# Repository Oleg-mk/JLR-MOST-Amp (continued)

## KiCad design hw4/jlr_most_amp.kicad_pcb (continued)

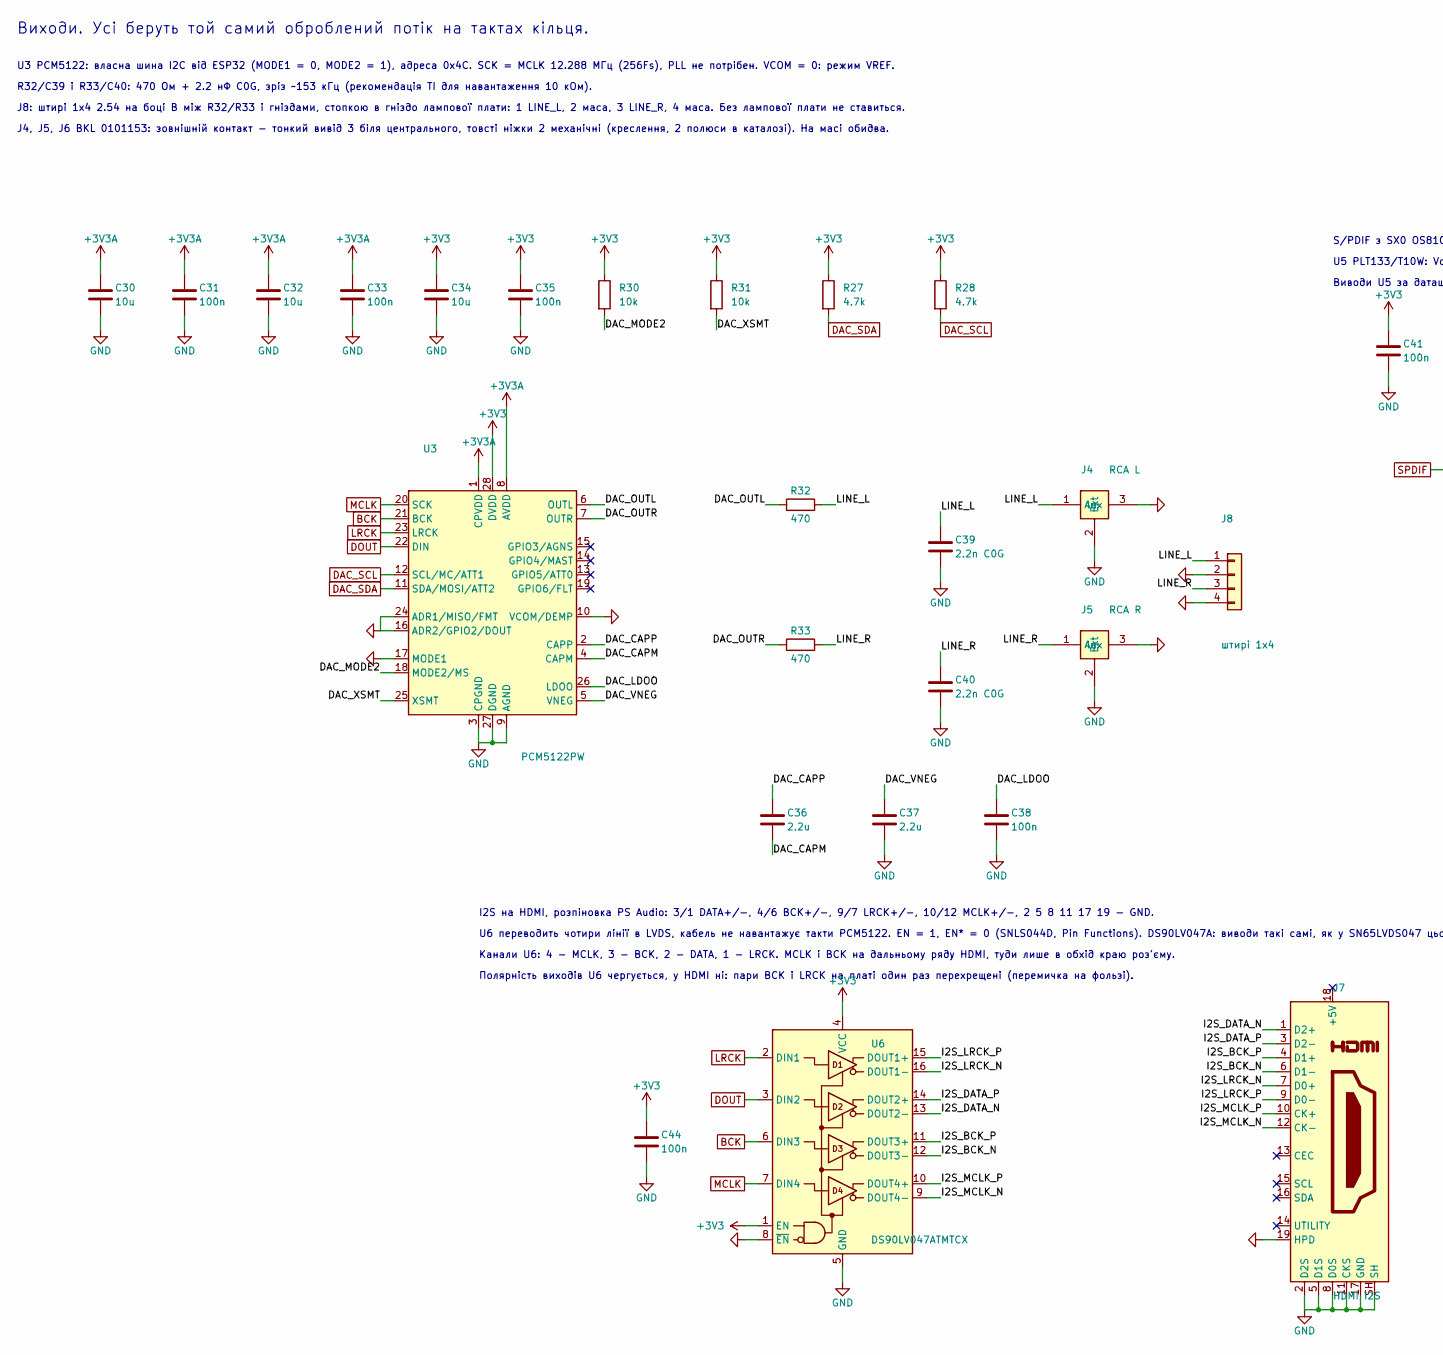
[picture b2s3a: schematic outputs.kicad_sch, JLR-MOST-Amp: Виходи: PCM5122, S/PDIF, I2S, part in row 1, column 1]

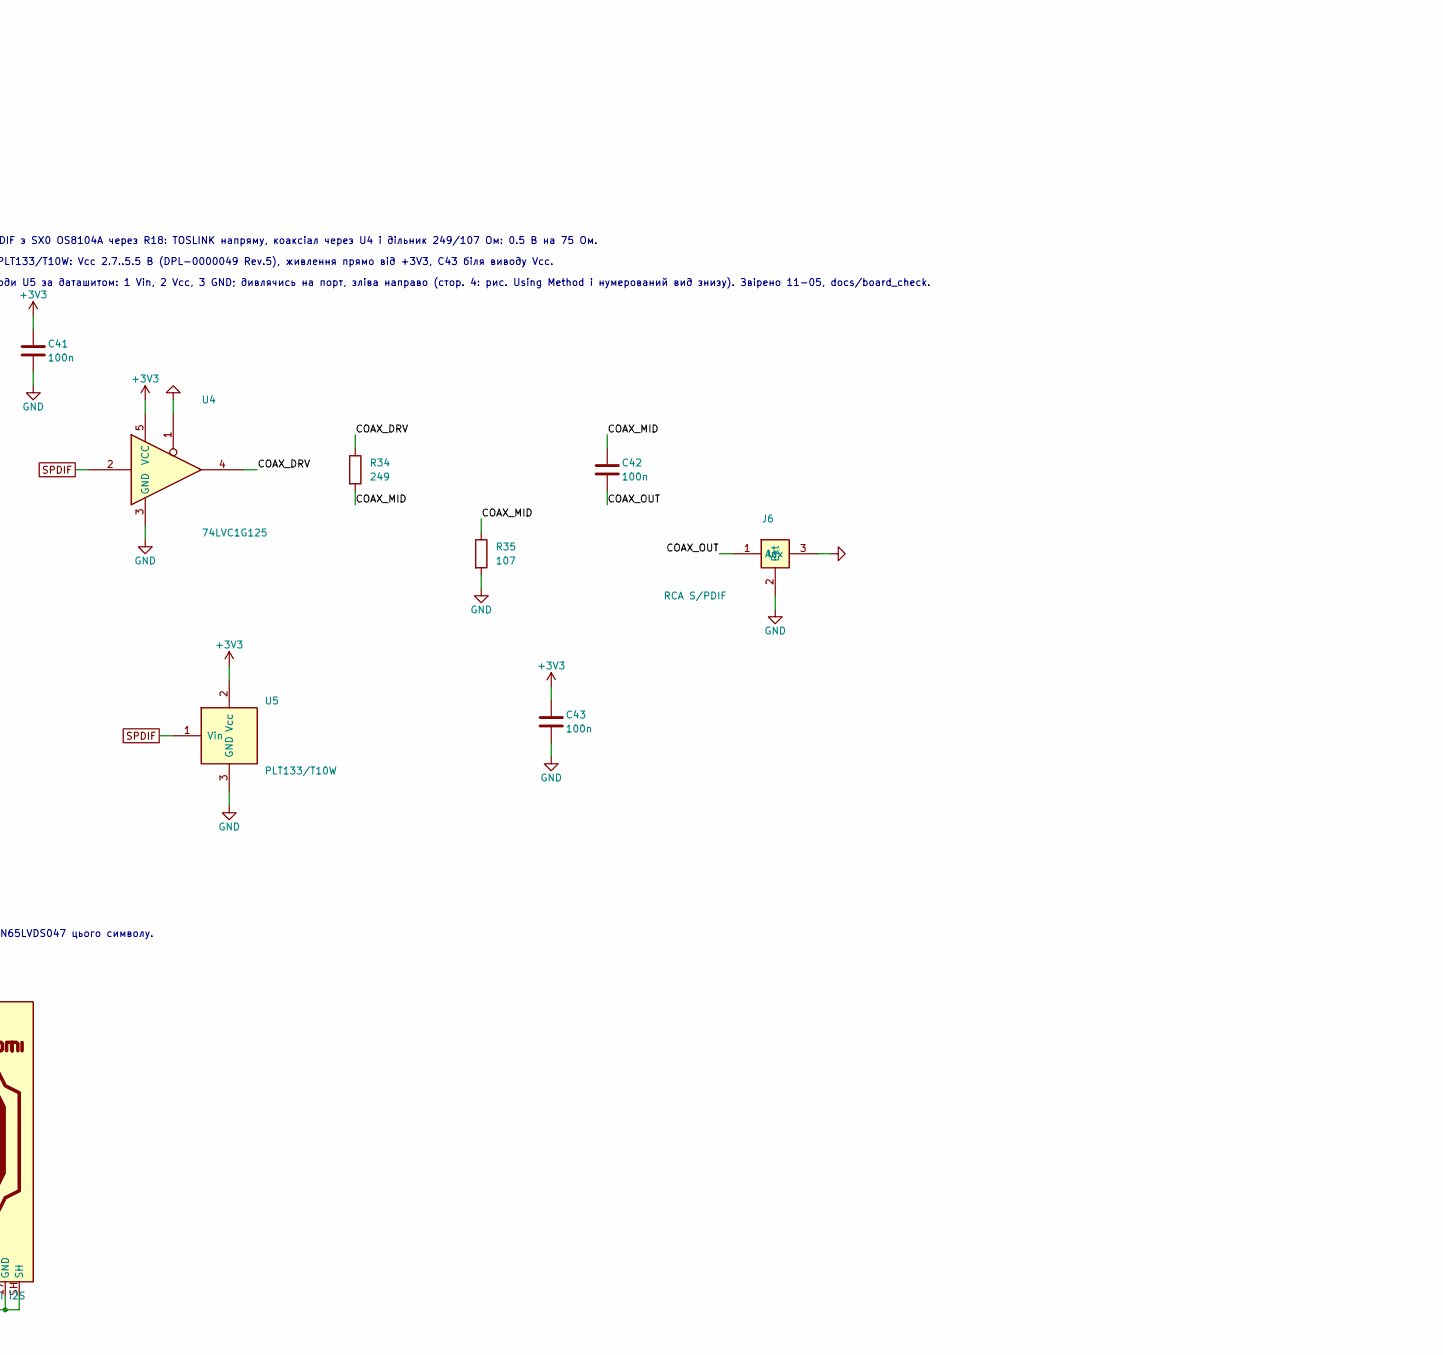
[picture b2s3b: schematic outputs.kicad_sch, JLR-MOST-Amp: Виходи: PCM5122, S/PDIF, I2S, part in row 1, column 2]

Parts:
C30, C32, C34: 10u; C_0805_2012Metric
C31, C33, C35, C38, C41, C42, C43, C44: 100n; C_0603_1608Metric
C36, C37: 2.2u; C_0805_2012Metric
C39, C40: 2.2n C0G; C_0603_1608Metric
J4: RCA L; BKL_0101153_RCA_RA
J5: RCA R; BKL_0101153_RCA_RA
J6: RCA S/PDIF; BKL_0101153_RCA_RA
J7: HDMI I2S; HDMI_A_Kycon_KDMIX-SL1-NS-WS-B15_VerticalRightAngle
J8: штирі 1x4; PinHeader_1x04_P2.54mm_Vertical
R27, R28: 4.7k; R_0603_1608Metric
R30, R31: 10k; R_0603_1608Metric
R32, R33: 470; R_0603_1608Metric
R34: 249; R_0603_1608Metric
R35: 107; R_0603_1608Metric
U3: PCM5122PW; TSSOP-28_4.4x9.7mm_P0.65mm
U4: 74LVC1G125; SOT-23-5
U5: PLT133/T10W; Everlight_TOSLINK_T10
U6: DS90LV047ATMTCX; TSSOP-16_4.4x5mm_P0.65mm

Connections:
+3V3: C34.1, C35.1, C41.1, C43.1, C44.1, R27.1, R28.1, R30.1, R31.1, U3.28 (DVDD), U4.5 (VCC), U5.2 (Vcc), U6.1 (EN), U6.4 (VCC); also elsewhere on the board
+3V3A: C30.1, C31.1, C32.1, C33.1, U3.1 (CPVDD), U3.8 (AVDD); also elsewhere on the board
/Виходи: PCM5122, S/PDIF, I2S/COAX_DRV: R34.1, U4.4
/Виходи: PCM5122, S/PDIF, I2S/COAX_MID: C42.1, R34.2, R35.1
/Виходи: PCM5122, S/PDIF, I2S/COAX_OUT: C42.2, J6.1 (In)
/Виходи: PCM5122, S/PDIF, I2S/DAC_CAPM: C36.2, U3.4 (CAPM)
/Виходи: PCM5122, S/PDIF, I2S/DAC_CAPP: C36.1, U3.2 (CAPP)
/Виходи: PCM5122, S/PDIF, I2S/DAC_LDOO: C38.1, U3.26 (LDOO)
/Виходи: PCM5122, S/PDIF, I2S/DAC_MODE2: R30.2, U3.18 (MODE2/MS)
/Виходи: PCM5122, S/PDIF, I2S/DAC_OUTL: R32.1, U3.6 (OUTL)
/Виходи: PCM5122, S/PDIF, I2S/DAC_OUTR: R33.1, U3.7 (OUTR)
/Виходи: PCM5122, S/PDIF, I2S/DAC_VNEG: C37.1, U3.5 (VNEG)
/Виходи: PCM5122, S/PDIF, I2S/DAC_XSMT: R31.2, U3.25 (XSMT)
/Виходи: PCM5122, S/PDIF, I2S/I2S_BCK_N: J7.6 (D1-), U6.12 (DOUT3-)
/Виходи: PCM5122, S/PDIF, I2S/I2S_BCK_P: J7.4 (D1+), U6.11 (DOUT3+)
/Виходи: PCM5122, S/PDIF, I2S/I2S_DATA_N: J7.1 (D2+), U6.13 (DOUT2-)
/Виходи: PCM5122, S/PDIF, I2S/I2S_DATA_P: J7.3 (D2-), U6.14 (DOUT2+)
/Виходи: PCM5122, S/PDIF, I2S/I2S_LRCK_N: J7.7 (D0+), U6.16 (DOUT1-)
/Виходи: PCM5122, S/PDIF, I2S/I2S_LRCK_P: J7.9 (D0-), U6.15 (DOUT1+)
/Виходи: PCM5122, S/PDIF, I2S/I2S_MCLK_N: J7.12 (CK-), U6.9 (DOUT4-)
/Виходи: PCM5122, S/PDIF, I2S/I2S_MCLK_P: J7.10 (CK+), U6.10 (DOUT4+)
/Виходи: PCM5122, S/PDIF, I2S/LINE_L: C39.1, J4.1 (In), J8.1, R32.2
/Виходи: PCM5122, S/PDIF, I2S/LINE_R: C40.1, J5.1 (In), J8.3, R33.2
BCK: U3.21 (BCK), U6.6 (DIN3); also elsewhere on the board
DAC_SCL: R28.2, U3.12 (SCL/MC/ATT1); also elsewhere on the board
DAC_SDA: R27.2, U3.11 (SDA/MOSI/ATT2); also elsewhere on the board
DOUT: U3.22 (DIN), U6.3 (DIN2); also elsewhere on the board
GND: C30.2, C31.2, C32.2, C33.2, C34.2, C35.2, C37.2, C38.2, C39.2, C40.2, C41.2, C43.2, C44.2, J4.2 (Ext), J4.3 (Aux), J5.2 (Ext), J5.3 (Aux), J6.2 (Ext), J6.3 (Aux), J7.2 (D2S), J7.5 (D1S), J7.8 (D0S), J7.11 (CKS), J7.17 (GND), J7.19 (HPD), J7.SH, J8.2, J8.4, R35.2, U3.3 (CPGND), U3.9 (AGND), U3.10 (VCOM/DEMP), U3.16 (ADR2/GPIO2/DOUT), U3.17 (MODE1), U3.24 (ADR1/MISO/FMT), U3.27 (DGND), U4.1, U4.3 (GND), U5.3 (GND), U6.5 (GND), U6.8 (~EN); also elsewhere on the board
LRCK: U3.23 (LRCK), U6.2 (DIN1); also elsewhere on the board
MCLK: U3.20 (SCK), U6.7 (DIN4); also elsewhere on the board
SPDIF: U4.2, U5.1 (Vin); also elsewhere on the board

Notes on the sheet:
Виходи. Усі беруть той самий оброблений потік на тактах кільця.
U3 PCM5122: власна шина I2C від ESP32 (MODE1 = 0, MODE2 = 1), адреса 0x4C. SCK = MCLK 12.288 МГц (256Fs), PLL не потрібен. VCOM = 0: режим VREF.
R32/C39 і R33/C40: 470 Ом + 2.2 нФ C0G, зріз ~153 кГц (рекомендація TI для навантаження 10 кОм).
J8: штирі 1x4 2.54 на боці B між R32/R33 і гніздами, стопкою в гніздо лампової плати: 1 LINE_L, 2 маса, 3 LINE_R, 4 маса. Без лампової плати не ставиться.
S/PDIF з SX0 OS8104A через R18: TOSLINK напряму, коаксіал через U4 і дільник 249/107 Ом: 0.5 В на 75 Ом.
U5 PLT133/T10W: Vcc 2.7..5.5 В (DPL-0000049 Rev.5), живлення прямо від +3V3, C43 біля виводу Vcc.
Виводи U5 за даташитом: 1 Vin, 2 Vcc, 3 GND; дивлячись на порт, зліва направо (стор. 4: рис. Using Method і нумерований вид знизу). Звірено 11-05, docs/board_check.
J4, J5, J6 BKL 0101153: зовнішній контакт - тонкий вивід 3 біля центрального, товсті ніжки 2 механічні (креслення, 2 полюси в каталозі). На масі обидва.
I2S на HDMI, розпіновка PS Audio: 3/1 DATA+/-, 4/6 BCK+/-, 9/7 LRCK+/-, 10/12 MCLK+/-, 2 5 8 11 17 19 - GND.
U6 переводить чотири лінії в LVDS, кабель не навантажує такти PCM5122. EN = 1, EN* = 0 (SNLS044D, Pin Functions). DS90LV047A: виводи такі самі, як у SN65LVDS047 цього символу.
Канали U6: 4 - MCLK, 3 - BCK, 2 - DATA, 1 - LRCK. MCLK і BCK на дальньому ряду HDMI, туди лише в обхід краю роз'єму.
Полярність виходів U6 чергується, у HDMI ні: пари BCK і LRCK на платі один раз перехрещені (перемичка на фользі).

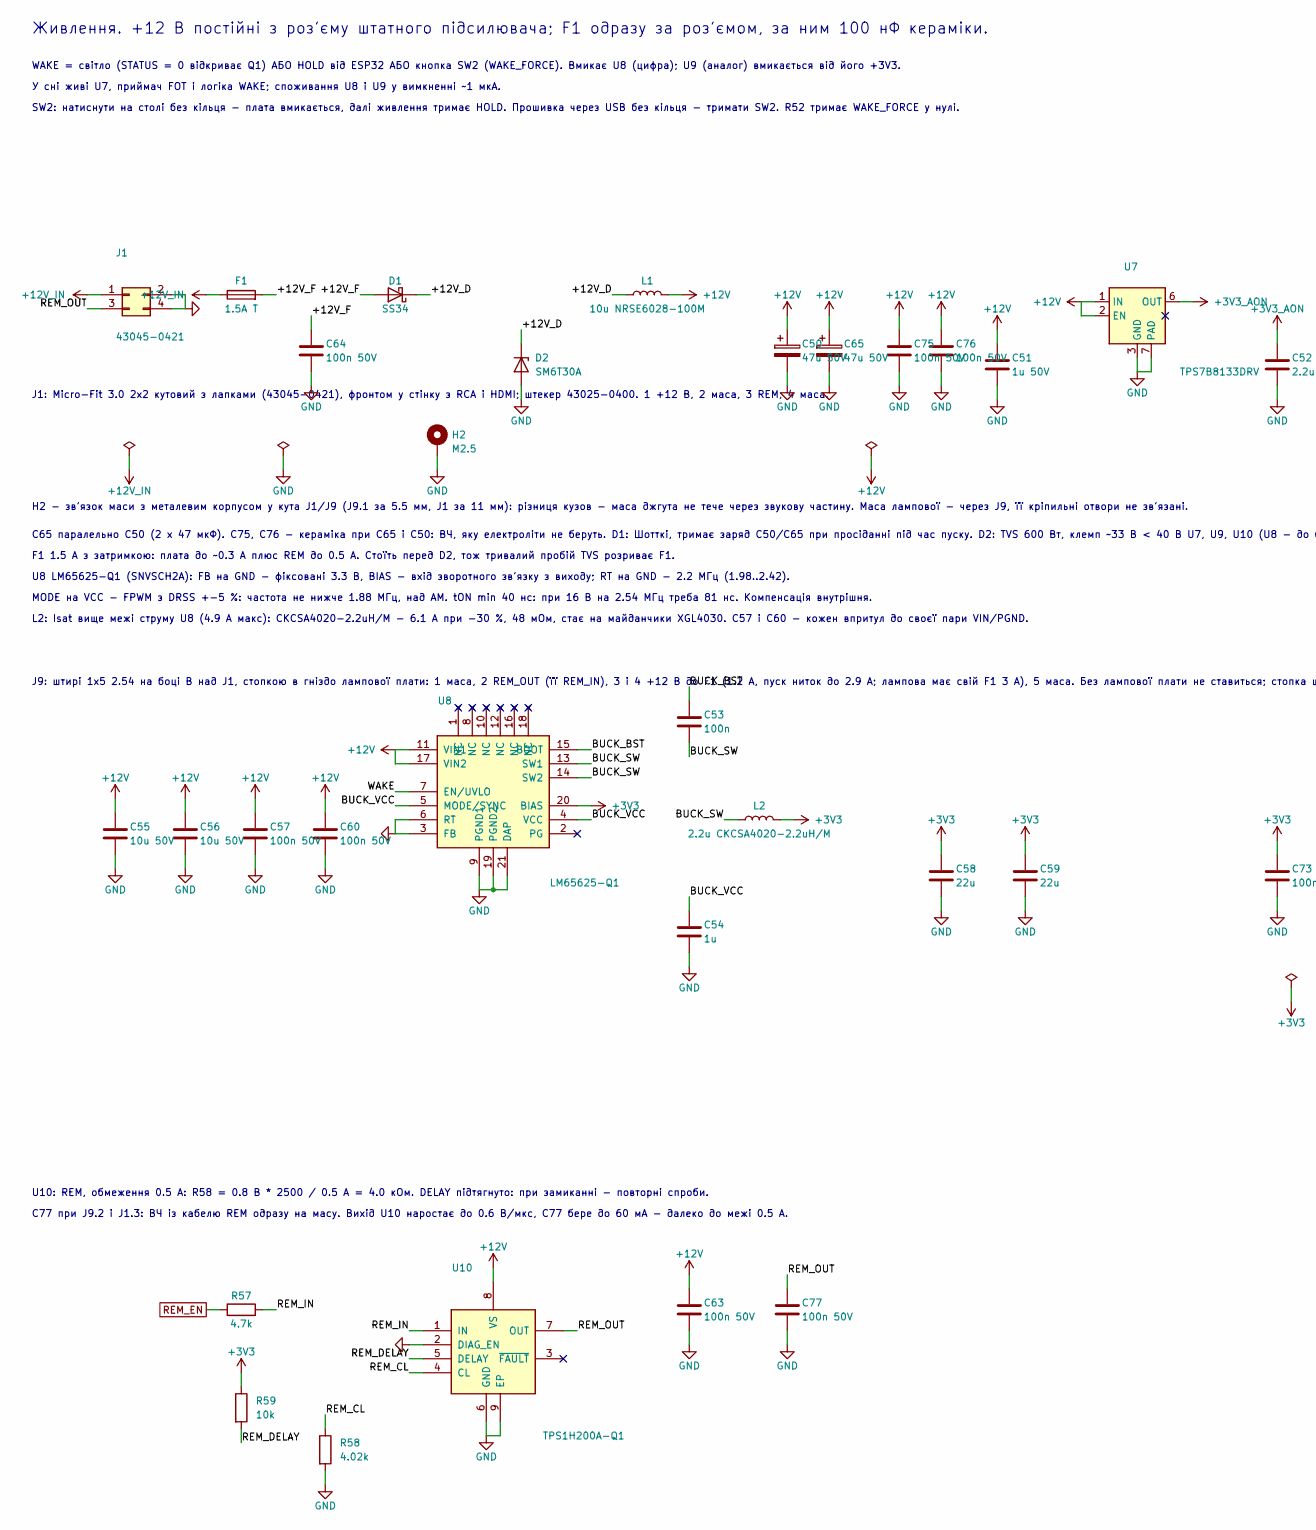
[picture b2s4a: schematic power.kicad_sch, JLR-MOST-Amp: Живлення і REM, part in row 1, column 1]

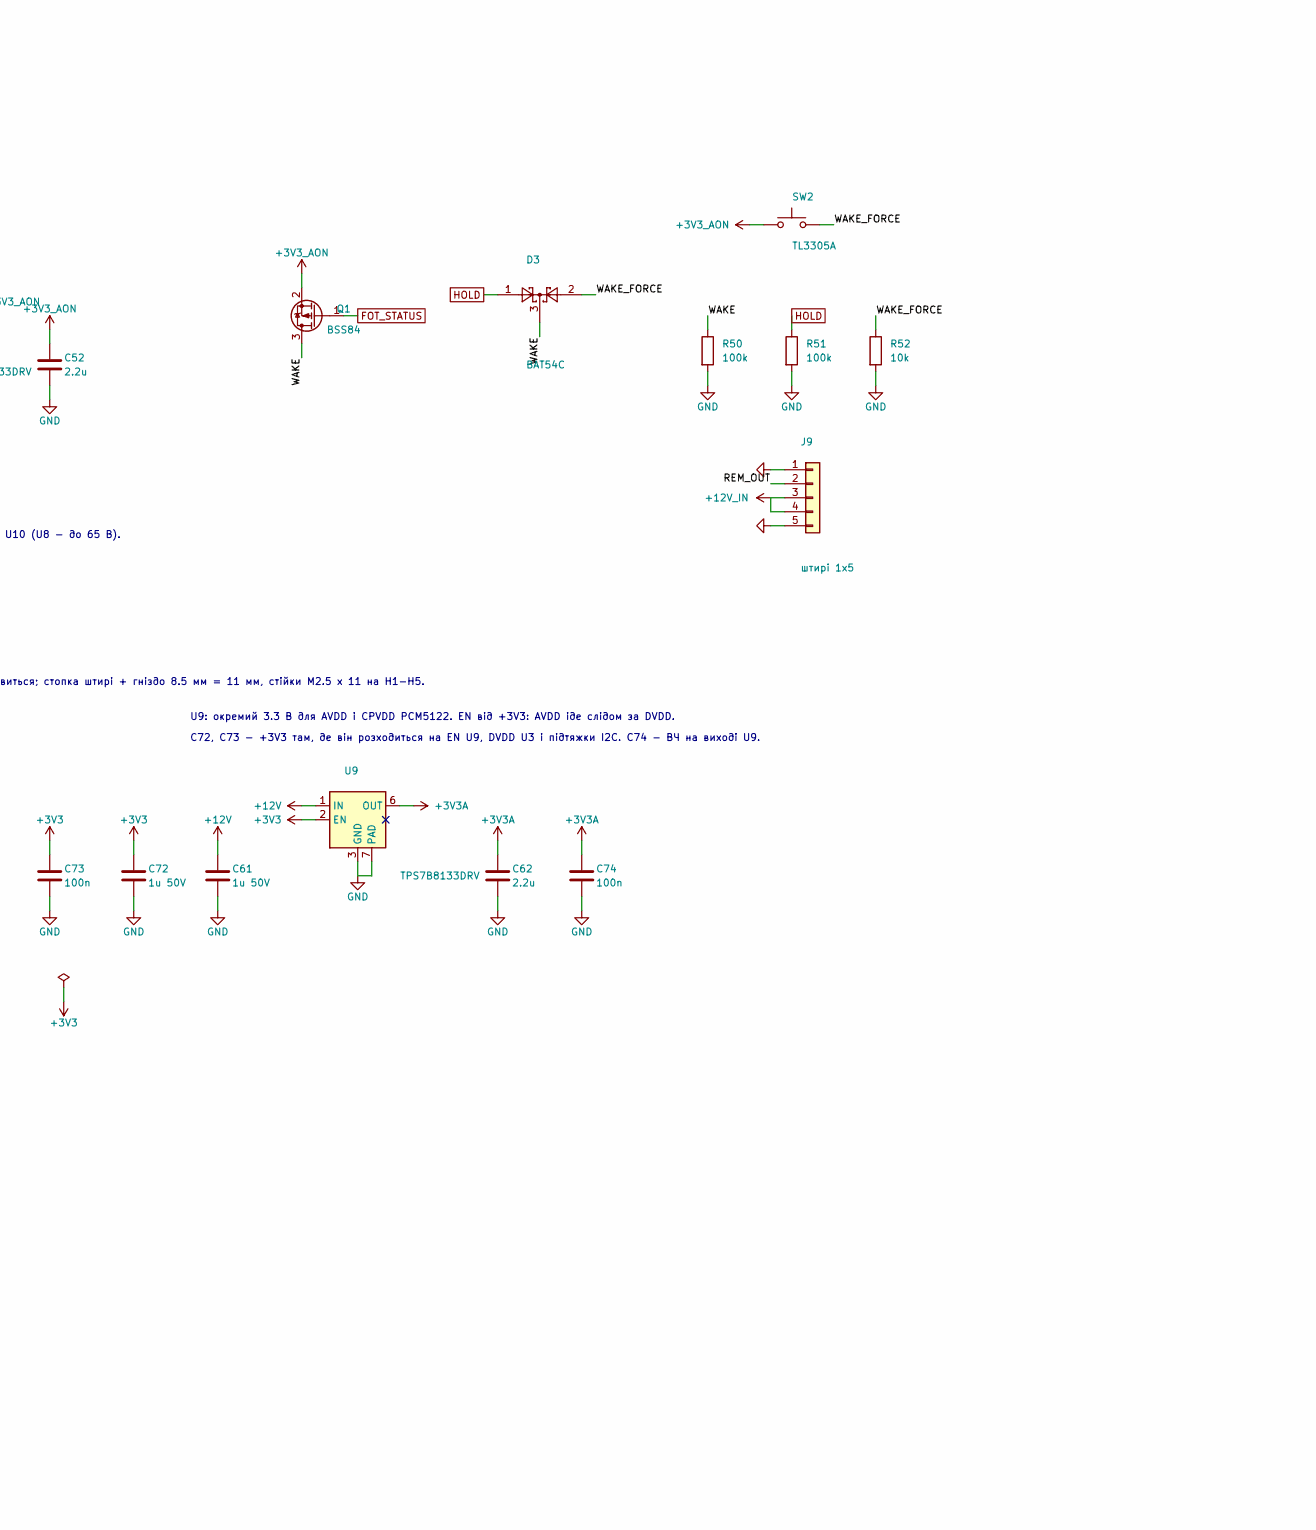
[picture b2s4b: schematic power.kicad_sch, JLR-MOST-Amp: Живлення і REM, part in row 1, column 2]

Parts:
C50, C65: 47u 50V; CP_Elec_8x10
C51, C61, C72: 1u 50V; C_0805_2012Metric
C52, C62: 2.2u; C_0805_2012Metric
C53, C73, C74: 100n; C_0603_1608Metric
C54: 1u; C_0603_1608Metric
C55, C56: 10u 50V; C_1210_3225Metric
C57, C60, C63, C64, C75, C76, C77: 100n 50V; C_0603_1608Metric
C58, C59: 22u; C_1206_3216Metric
D1: SS34; D_SMA
D2: SM6T30A; D_SMB
D3: BAT54C; SOT-23
F1: 1.5A T; Fuse_1206_3216Metric
H2: M2.5; MountingHole_2.7mm_M2.5_Standoff_GND
J1: 43045-0421; Molex_Micro-Fit_3.0_43045-0421_2x02-1MP_P3.00mm_Horizontal
J9: штирі 1x5; PinHeader_1x05_P2.54mm_Vertical
L1: 10u NRSE6028-100M; L_Bourns-SRN6028
L2: 2.2u CKCSA4020-2.2uH/M; L_Coilcraft_XxL4030
Q1: BSS84; SOT-23
R50, R51: 100k; R_0603_1608Metric
R52, R59: 10k; R_0603_1608Metric
R57: 4.7k; R_0603_1608Metric
R58: 4.02k; R_0603_1608Metric
SW2: TL3305A; SW_SPST_TL3305A
U7, U9: TPS7B8133DRV; WSON-6-1EP_2x2mm_P0.65mm_EP1x1.6mm
U8: LM65625-Q1; TI_RZT0020A
U10: TPS1H200A-Q1; HVSSOP-8-1EP_3x3mm_P0.65mm_EP1.57x1.89mm

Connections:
+3V3: C58.1, C59.1, C72.1, C73.1, L2.2, R59.1, U8.20 (BIAS), U9.2 (EN); also elsewhere on the board
+3V3A: C62.1, C74.1, U9.6 (OUT); also elsewhere on the board
+3V3_AON: C52.1, Q1.2 (S), SW2.1, U7.6 (OUT); also elsewhere on the board
+12V: C50.1, C51.1, C55.1, C56.1, C57.1, C60.1, C61.1, C63.1, C65.1, C75.1, C76.1, L1.2, U7.1 (IN), U7.2 (EN), U8.11 (VIN1), U8.17 (VIN2), U9.1 (IN), U10.8 (VS)
+12V_IN: F1.1, J1.1, J9.3, J9.4
/Живлення і REM/+12V_D: D1.1 (K), D2.1 (K), L1.1
/Живлення і REM/+12V_F: C64.1, D1.2 (A), F1.2
/Живлення і REM/BUCK_BST: C53.1, U8.15 (BOOT)
/Живлення і REM/BUCK_SW: C53.2, L2.1, U8.13 (SW1), U8.14 (SW2)
/Живлення і REM/BUCK_VCC: C54.1, U8.4 (VCC), U8.5 (MODE/SYNC)
/Живлення і REM/REM_CL: R58.1, U10.4 (CL)
/Живлення і REM/REM_DELAY: R59.2, U10.5 (DELAY)
/Живлення і REM/REM_IN: R57.2, U10.1 (IN)
/Живлення і REM/REM_OUT: C77.1, J1.3, J9.2, U10.7 (OUT)
/Живлення і REM/WAKE: D3.3, Q1.3 (D), R50.1, U8.7 (EN/UVLO)
/Живлення і REM/WAKE_FORCE: D3.2, R52.1, SW2.2
FOT_STATUS: Q1.1 (G); also elsewhere on the board
GND: C50.2, C51.2, C52.2, C54.2, C55.2, C56.2, C57.2, C58.2, C59.2, C60.2, C61.2, C62.2, C63.2, C64.2, C65.2, C72.2, C73.2, C74.2, C75.2, C76.2, C77.2, D2.2 (A), H2.1, J1.2, J1.4, J9.1, J9.5, R50.2, R51.2, R52.2, R58.2, U7.3 (GND), U7.4 (GND), U7.7 (PAD), U8.3 (FB), U8.6 (RT), U8.9 (PGND1), U8.19 (PGND2), U8.21 (DAP), U9.3 (GND), U9.4 (GND), U9.7 (PAD), U10.2 (DIAG_EN), U10.6 (GND), U10.9 (EP); also elsewhere on the board
HOLD: D3.1, R51.1; also elsewhere on the board
REM_EN: R57.1; also elsewhere on the board

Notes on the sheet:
Живлення. +12 В постійні з роз'єму штатного підсилювача; F1 одразу за роз'ємом, за ним 100 нФ кераміки.
WAKE = світло (STATUS = 0 відкриває Q1) АБО HOLD від ESP32 АБО кнопка SW2 (WAKE_FORCE). Вмикає U8 (цифра); U9 (аналог) вмикається від його +3V3.
У сні живі U7, приймач FOT і логіка WAKE; споживання U8 і U9 у вимкненні ~1 мкА.
SW2: натиснути на столі без кільця - плата вмикається, далі живлення тримає HOLD. Прошивка через USB без кільця - тримати SW2. R52 тримає WAKE_FORCE у нулі.
J1: Micro-Fit 3.0 2x2 кутовий з лапками (43045-0421), фронтом у стінку з RCA і HDMI; штекер 43025-0400. 1 +12 В, 2 маса, 3 REM, 4 маса.
J9: штирі 1x5 2.54 на боці B над J1, стопкою в гніздо лампової плати: 1 маса, 2 REM_OUT (її REM_IN), 3 і 4 +12 В до F1 (1.2 А, пуск ниток до 2.9 А; лампова має свій F1 3 А), 5 маса. Без лампової плати не ставиться; стопка штирі + гніздо 8.5 мм = 11 мм, стійки M2.5 x 11 на H1-H5.
H2 - зв'язок маси з металевим корпусом у кута J1/J9 (J9.1 за 5.5 мм, J1 за 11 мм): різниця кузов - маса джгута не тече через звукову частину. Маса лампової - через J9, її кріпильні отвори не зв'язані.
C65 паралельно C50 (2 x 47 мкФ). C75, C76 - кераміка при C65 і C50: ВЧ, яку електроліти не беруть. D1: Шотткі, тримає заряд C50/C65 при просіданні під час пуску. D2: TVS 600 Вт, клемп ~33 В < 40 В U7, U9, U10 (U8 - до 65 В).
F1 1.5 А з затримкою: плата до ~0.3 А плюс REM до 0.5 А. Стоїть перед D2, тож тривалий пробій TVS розриває F1.
U8 LM65625-Q1 (SNVSCH2A): FB на GND - фіксовані 3.3 В, BIAS - вхід зворотного зв'язку з виходу; RT на GND - 2.2 МГц (1.98..2.42).
MODE на VCC - FPWM з DRSS +-5 %: частота не нижче 1.88 МГц, над AM. tON min 40 нс: при 16 В на 2.54 МГц треба 81 нс. Компенсація внутрішня.
L2: Isat вище межі струму U8 (4.9 А макс): CKCSA4020-2.2uH/M - 6.1 А при -30 %, 48 мОм, стає на майданчики XGL4030. C57 і C60 - кожен впритул до своєї пари VIN/PGND.
U9: окремий 3.3 В для AVDD і CPVDD PCM5122. EN від +3V3: AVDD іде слідом за DVDD.
C72, C73 - +3V3 там, де він розходиться на EN U9, DVDD U3 і підтяжки I2C. C74 - ВЧ на виході U9.
U10: REM, обмеження 0.5 А: R58 = 0.8 В * 2500 / 0.5 А = 4.0 кОм. DELAY підтягнуто: при замиканні - повторні спроби.
C77 при J9.2 і J1.3: ВЧ із кабелю REM одразу на масу. Вихід U10 наростає до 0.6 В/мкс, C77 бере до 60 мА - далеко до межі 0.5 А.

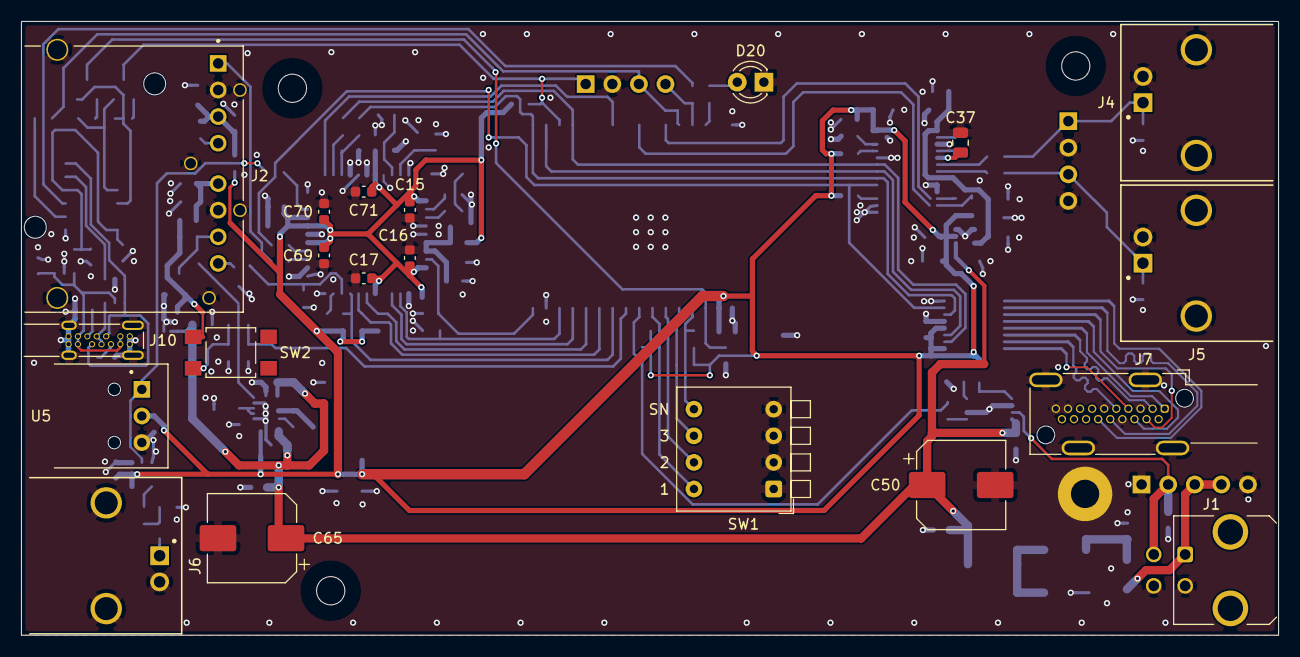
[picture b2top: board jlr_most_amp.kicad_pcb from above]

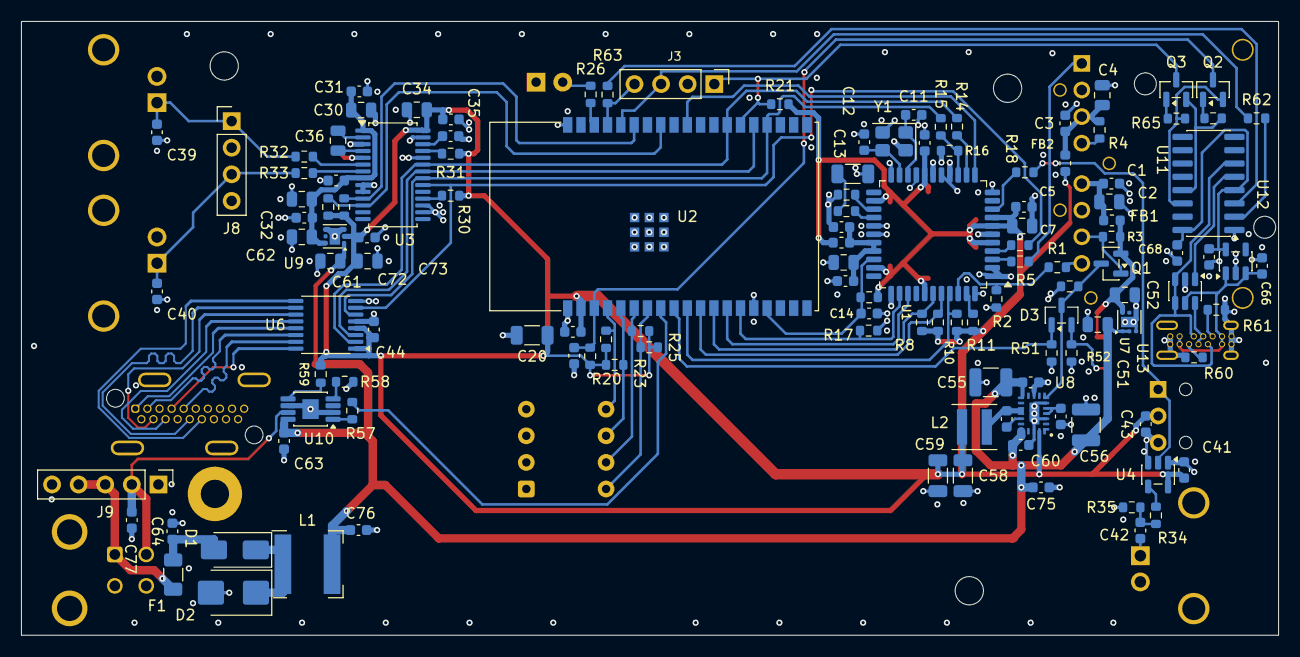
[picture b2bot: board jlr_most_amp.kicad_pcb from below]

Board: 4 copper layers, 120.1 x 58.6 mm, 151 parts (131 on the bottom side), 95 nets.

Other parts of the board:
H1, H3, H4: M2.5; MountingHole_2.7mm_M2.5_Standoff

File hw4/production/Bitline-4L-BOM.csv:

Comment,Designator,Footprint,Quantity,LCSC Part #
100n,"C1,C3,C5,C6,C8,C9,C15,C16,C17,C21,C31,C33,C35,C38,C41,C42,C43,C44,C53,C68,C69,C70,C71,C73,C74",C_0603_1608Metric,25,
10u,"C2,C4,C7,C10,C30,C32,C34",C_0805_2012Metric,7,
18p,"C11,C12",C_0603_1608Metric,2,
100n C0G,C13,C_1206_3216Metric,1,
1u,"C14,C22,C54,C66,C67",C_0603_1608Metric,5,
22u,"C20,C58,C59",C_1206_3216Metric,3,
2.2u,"C36,C37,C52,C62",C_0805_2012Metric,4,
2.2n C0G,"C39,C40",C_0603_1608Metric,2,
47u 50V,"C50,C65",CP_Elec_8x10,2,
1u 50V,"C51,C61,C72",C_0805_2012Metric,3,
10u 50V,"C55,C56",C_1210_3225Metric,2,
100n 50V,"C57,C60,C63,C64,C75,C76,C77",C_0603_1608Metric,7,
SS34,D1,D_SMA,1,
SM6T30A,D2,D_SMB,1,
BAT54C,D3,SOT-23,1,
LED 3 mm,D20,LED_D3.0mm,1,
1.5A T,F1,Fuse_1206_3216Metric,1,
600R@100MHz,"FB1,FB2,FB3",L_0603_1608Metric,3,
43045-0421,J1,Molex_Micro-Fit_3.0_43045-0421_2x02-1MP_P3.00mm_Horizontal,1,
TE 1-1394640-1,J2,TE_MOST_Pigtail_FOT_2+0,1,
RCA L,J4,BKL_0101153_RCA_RA,1,
RCA R,J5,BKL_0101153_RCA_RA,1,
RCA S/PDIF,J6,BKL_0101153_RCA_RA,1,
HDMI I2S,J7,HDMI_A_Kycon_KDMIX-SL1-NS-WS-B15_VerticalRightAngle,1,
штирі 1x4,J8,PinHeader_1x04_P2.54mm_Vertical,1,
штирі 1x5,J9,PinHeader_1x05_P2.54mm_Vertical,1,
USB-C,J10,USB_C_Receptacle_14P_SideInsert_THT,1,
10u NRSE6028-100M,L1,L_Bourns-SRN6028,1,
2.2u CKCSA4020-2.2uH/M,L2,L_Coilcraft_XxL4030,1,
BSS84,Q1,SOT-23,1,
MMBT3904,"Q2,Q3",SOT-23,2,
100,"R1,R5",R_0603_1608Metric,2,
100k,"R2,R17,R50,R51",R_0603_1608Metric,4,
47k,"R3,R7,R10,R11",R_0603_1608Metric,4,
15k,R4,R_0603_1608Metric,1,
2.2k,R6,R_0603_1608Metric,1,
4.7k,"R8,R9,R27,R28,R57,R62,R63",R_0603_1608Metric,7,
10k,"R12,R16,R20,R21,R22,R23,R24,R25,R30,R31,R52,R59,R64,R65",R_0603_1608Metric,14,
68,"R13,R18",R_0603_1608Metric,2,
47,"R14,R15",R_0603_1608Metric,2,
1k,R26,R_0603_1608Metric,1,
470,"R32,R33",R_0603_1608Metric,2,
249,R34,R_0603_1608Metric,1,
107,R35,R_0603_1608Metric,1,
4.02k,R58,R_0603_1608Metric,1,
5.1k,"R60,R61",R_0603_1608Metric,2,
DP-04 Piano,SW1,SW_DIP_SPSTx04_Piano_10.8x11.72mm_W7.62mm_P2.54mm,1,
TL3305A,SW2,SW_SPST_TL3305A,1,
OS8104AAQ,U1,LQFP-44_10x10mm_P0.8mm,1,
ESP32-WROVER-IE-N16R8,U2,ESP32-WROVER-IE,1,
PCM5122PW,U3,TSSOP-28_4.4x9.7mm_P0.65mm,1,
74LVC1G125,U4,SOT-23-5,1,
PLT133/T10W,U5,Everlight_TOSLINK_T10,1,
DS90LV047ATMTCX,U6,TSSOP-16_4.4x5mm_P0.65mm,1,
TPS7B8133DRV,"U7,U9",WSON-6-1EP_2x2mm_P0.65mm_EP1x1.6mm,2,
LM65625-Q1,U8,TI_RZT0020A,1,
TPS1H200A-Q1,U10,HVSSOP-8-1EP_3x3mm_P0.65mm_EP1.57x1.89mm,1,
CH340C,U11,SOIC-16_3.9x9.9mm_P1.27mm,1,
AP2112K-3.3,U12,SOT-23-5,1,
USBLC6-2SC6,U13,SOT-23-6,1,
12.288MHz,Y1,Crystal_SMD_3225-4Pin_3.2x2.5mm,1,

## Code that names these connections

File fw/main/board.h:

#pragma once
/* ESP32-WROVER-IE pins as wired on the main board (hw/gen/build.py, host sheet) */
#include <stdbool.h>
#include <stdint.h>
#include "driver/gpio.h"

#define PIN_BCK        GPIO_NUM_15   /* in: BCK 64Fs = 3.072 MHz from OS8104A, both I2S */
#define PIN_LRCK       GPIO_NUM_4    /* in: LRCK = FSY 48 kHz from OS8104A, both I2S */
#define PIN_MOST_SX1   GPIO_NUM_14   /* in: I2S0 data from SX1 */
#define PIN_SPDIF_SRC  GPIO_NUM_12   /* out: I2S0 data to SR1, OS8104A makes S/PDIF of it; strapping pin, R17 holds it low */
#define PIN_MOST_SX3   GPIO_NUM_5    /* in: I2S1 data from SX3 */
#define PIN_DOUT       GPIO_NUM_2    /* out: I2S1 data to PCM5122 and the HDMI LVDS driver */
#define PIN_MOST_SDA   GPIO_NUM_26   /* I2C0: OS8104A */
#define PIN_MOST_SCL   GPIO_NUM_27
#define PIN_MOST_INT   GPIO_NUM_25   /* in: OS8104A interrupt, active low, R10 pull-up */
#define PIN_MOST_RST   GPIO_NUM_13   /* open drain: OS8104A reset, R12 + C14 make the power-on reset */
#define PIN_DAC_SDA    GPIO_NUM_21   /* I2C1: PCM5122 */
#define PIN_DAC_SCL    GPIO_NUM_19
#define PIN_HOLD       GPIO_NUM_33   /* out: keeps the supply on after the light in the ring is gone */
#define PIN_REM_EN     GPIO_NUM_32   /* out: REM +12 V switch */
#define PIN_LED        GPIO_NUM_22   /* out: D20 */
#define PIN_MODE0      GPIO_NUM_36   /* in: SW1 key 4, "read serial number"; a closed key reads 0 */
#define PIN_MODE1      GPIO_NUM_39   /* in: SW1 keys 3, 2, 1 = MODE1, MODE2, MODE3: amplifier type */
#define PIN_MODE2      GPIO_NUM_34
#define PIN_MODE3      GPIO_NUM_35
#define PIN_TXD0       GPIO_NUM_1    /* out: UART0 TX to the CH340C (log and console) */

#define I2C_ADDR_OS8104A  0x23       /* 0x46 / 0x47 on the wire, AD0 = AD1 = 1 */
#define I2C_ADDR_PCM5122  0x4C

void board_init(void);
void board_hold(bool on);
void board_rem(bool on);
void board_led(bool on);
bool board_hold_get(void);
bool board_rem_get(void);
/* SW1: bit 0 = key 4 (read serial number), bits 1..3 = keys 3..1 (type); a set bit is a closed key */
uint8_t board_switch(void);
